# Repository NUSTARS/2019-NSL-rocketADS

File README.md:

# rocketADS
Software and Hardware for an active drag system for the Nasa Student Launch Competition

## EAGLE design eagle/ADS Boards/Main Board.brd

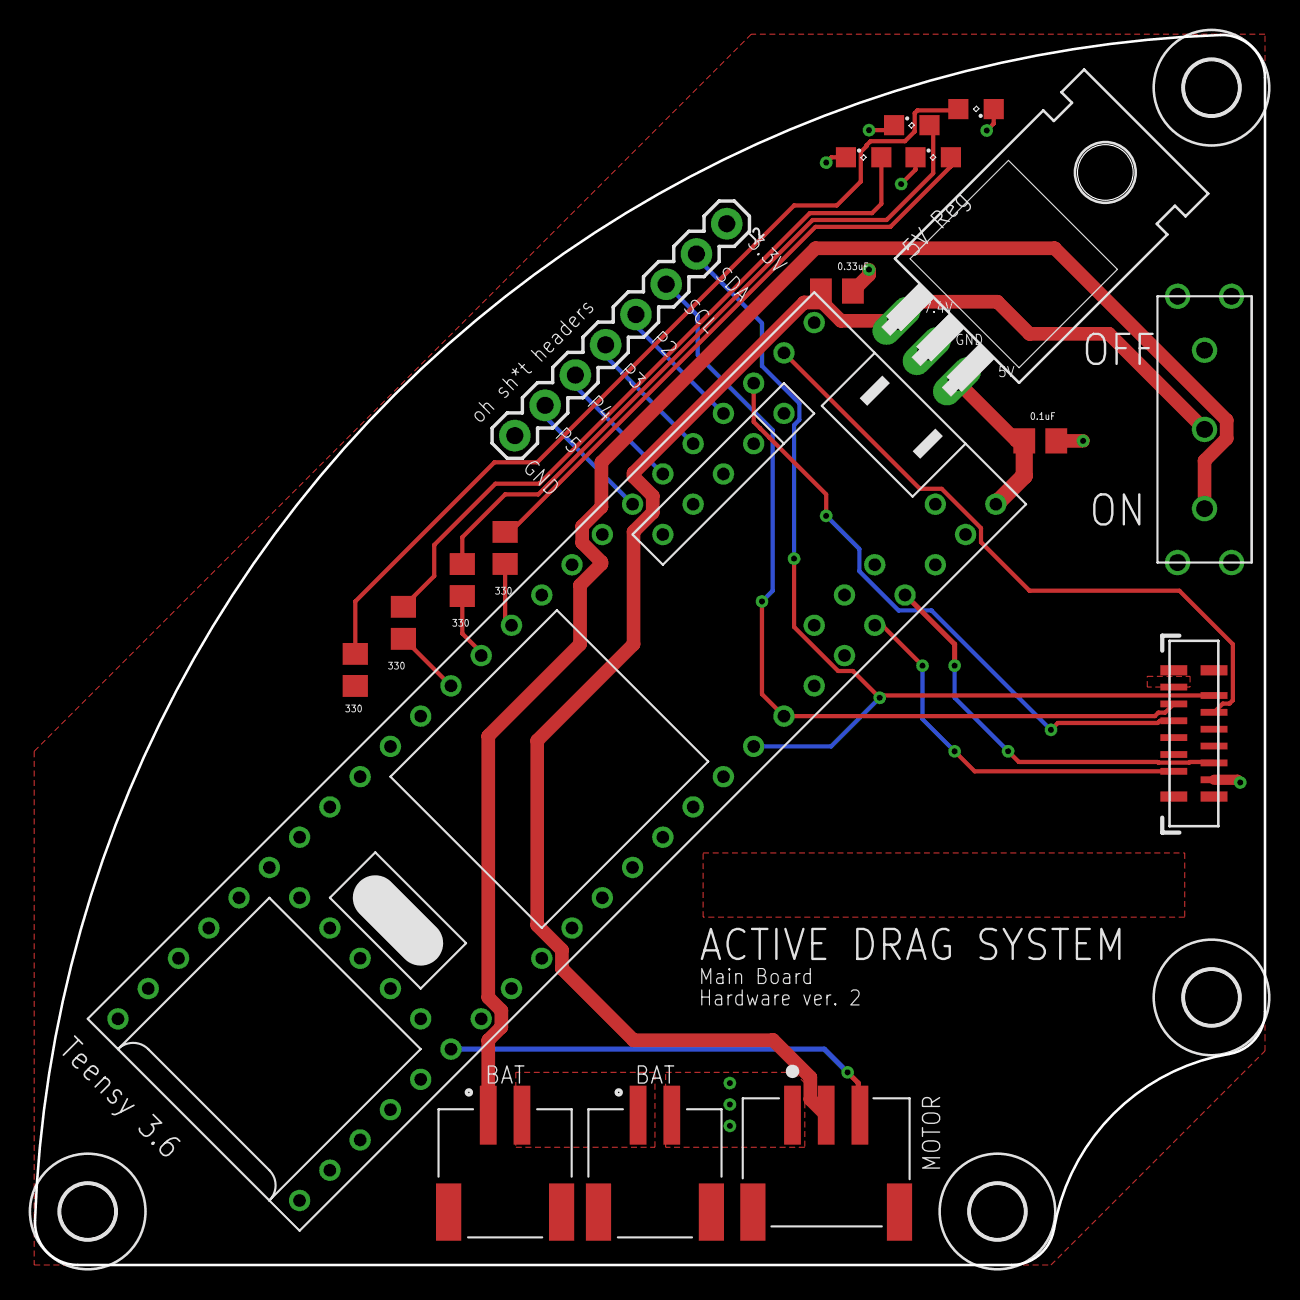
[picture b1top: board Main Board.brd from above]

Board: 2 copper layers, 73.0 x 73.0 mm, 22 parts (0 on the bottom side), 24 nets.

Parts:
BATTERY1, BATTERY2: S2B-PH-SM4-TB(LF)(SN); JST_S2B-PH-SM4-TB(LF)(SN)
C3: 0.33uF; C0805
C4: 0.1uF; C0805
H1, H2, H3, H4: MOUNT-HOLE3.2; 3,2
IC1: 7808T; TO220H
J1: 62674-121121ALF; CON12_1X12_DUT_58XF
J2: 1X08
LED1, LED2, LED3, LED4: SML0805
MOTOR: S3B-PH-SM4-TB(LF)(SN); JST_S3B-PH-SM4-TB(LF)(SN)
R1, R2, R3, R4: 330; R0805
U$1: TEENSY3.6
U$4: SLIDE_SWITCH2

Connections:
3.3V: J1.1, J2.1, R1.2, U$1.3.3V0, U$1.3.3V1, U$1.3.3V2
5V: C4.1, IC1.3, U$1.VIN
ADR: J1.11, U$1.P22
B1: J1.4, U$1.P0
B2: J1.5, U$1.P1
B3: J2.4, U$1.P2
B4: J2.5, U$1.P3
B5: J2.6, U$1.P4
B6: J2.7, U$1.P5
ERROR_LED: R3.2, U$1.P10
GND: BATTERY1.2, C3.2, C4.2, IC1.2, J1.12, J2.8, LED1.C, LED2.C, LED3.C, LED4.C, MOTOR.1, U$1.GND, U$1.GND0, U$1.GND2, U$4.OUT1
MISC_LED: R4.2, U$1.P11
MOTOR: MOTOR.3, U$1.P38
unnamed: LED1.A, R1.1
unnamed: BATTERY1.1, BATTERY2.2
unnamed: LED2.A, R2.1
unnamed: LED3.A, R3.1
unnamed: LED4.A, R4.1
RST: J1.10, U$1.P23
SCL: J1.3, J2.3, U$1.P19
SDA: J1.2, J2.2, U$1.P18
STATUS_LED: R2.2, U$1.P9
V_BATT: BATTERY2.1, U$4.OUT2
V_IN: C3.1, IC1.1, MOTOR.2, U$4.IN

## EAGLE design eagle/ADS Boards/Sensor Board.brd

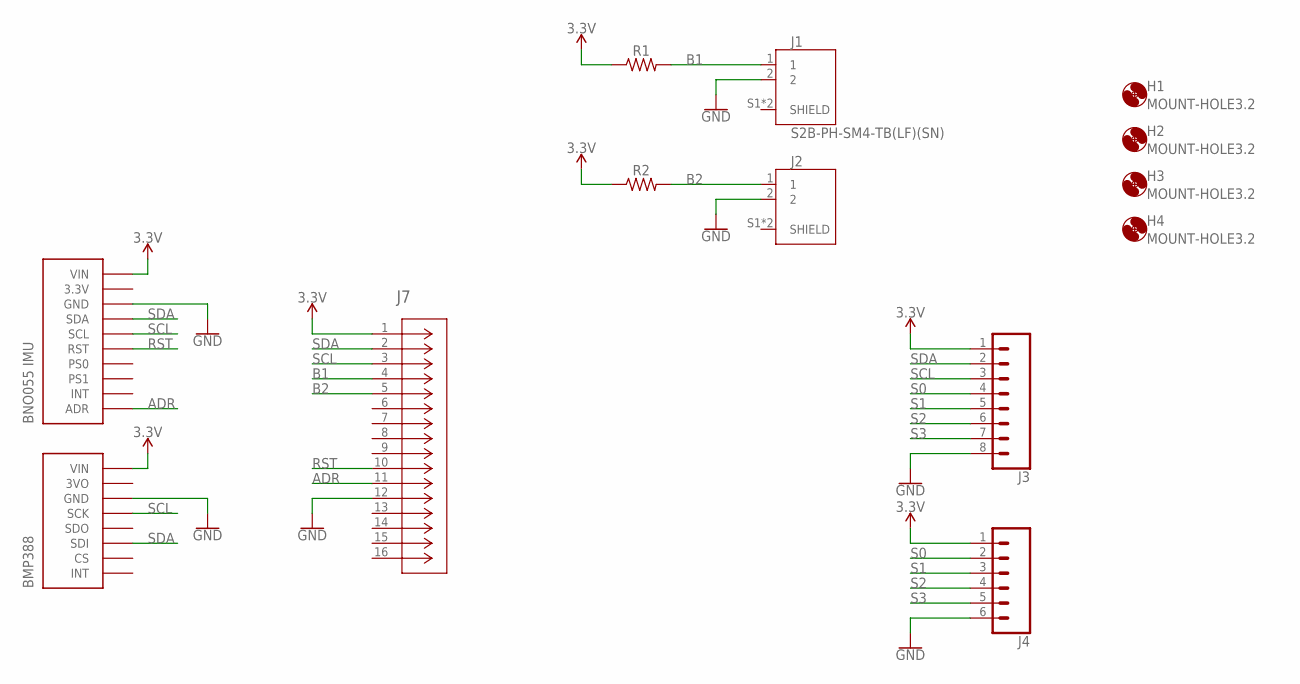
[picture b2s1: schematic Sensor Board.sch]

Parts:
H1, H2, H3, H4: MOUNT-HOLE3.2; 3,2
J1, J2: S2B-PH-SM4-TB(LF)(SN); JST_S2B-PH-SM4-TB(LF)(SN)
J3: CONN_08"; 1X08
J4: CONN_06SILK_FEMALE_PTH; 1X06
J7: 62674-121121ALF; CON12_1X12_DUT_58XF
R1, R2: 10k; R0805
U$1: BMP388
U$2: BNO055

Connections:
3.3V: J3.1, J4.1, J7.1 (11), R1.1, R2.1, U$1.VIN, U$2.VIN
ADR: J7.11 (1111), U$2.ADR
B1: J1.1, J7.4 (44), R1.2
B2: J2.1, J7.5 (55), R2.2
GND: J1.2, J2.2, J3.8, J4.6, J7.12 (1212), U$1.GND, U$2.GND
RST: J7.10 (1010), U$2.RST
S0: J3.4, J4.2
S1: J3.5, J4.3
S2: J3.6, J4.4
S3: J3.7, J4.5
SCL: J3.3, J7.3 (33), U$1.SCK, U$2.SCL
SDA: J3.2, J7.2 (22), U$1.SDI, U$2.SDA

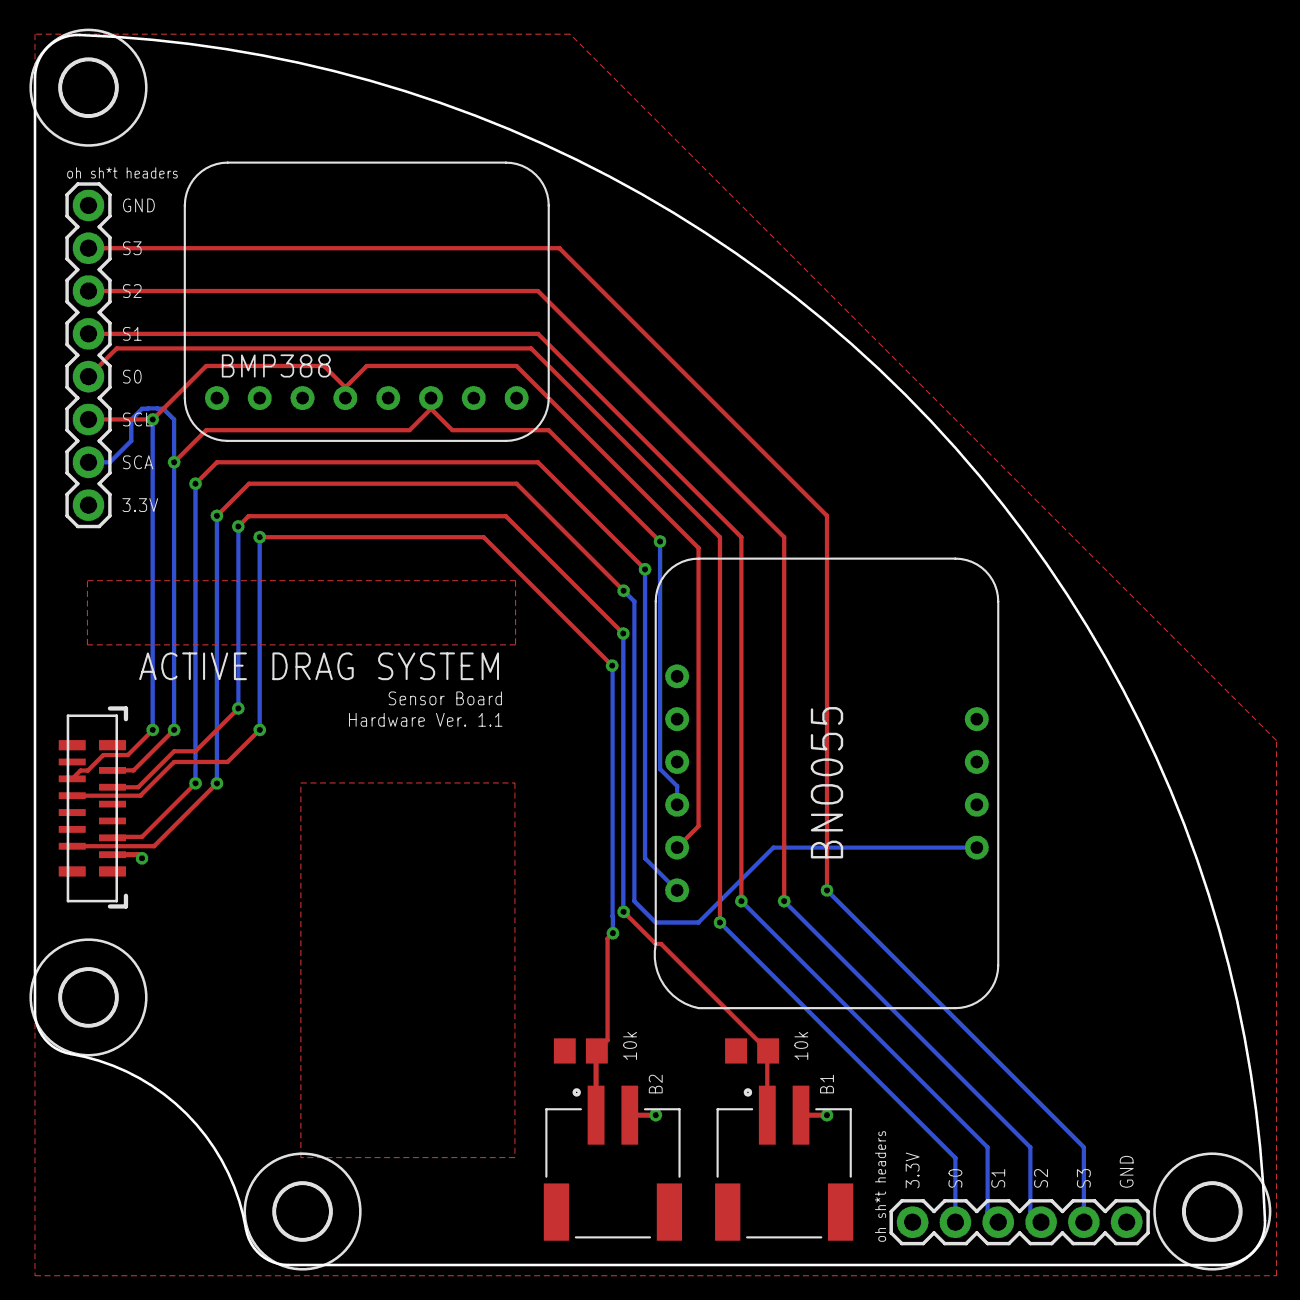
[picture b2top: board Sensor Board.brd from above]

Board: 2 copper layers, 73.0 x 73.0 mm, 13 parts (0 on the bottom side), 12 nets.

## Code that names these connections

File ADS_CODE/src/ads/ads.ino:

//#include <pid.h>
#include "sensors.h"
#include "storage.h"
#include <string>
#include <Servo.h>


#define STATUS_LED 10
#define ERROR_LED 9
#define BUILT_IN_LED 13
#define MISC_LED 11

#define BURNOUT_TIME 3500
#define APOGEE_TIME  17000

#define SERVO_CLOSE 750 //TODO: see if this can be used elsewhere in the code, as there are references to 750 where this is not used
#define SERVO_OPEN 2248

#define CLOSED_SERVO_PIN 0
#define OPEN_SERVO_PIN 1

#define SERVO_STEP_SIZE 50

using namespace nustars;


IntervalTimer timer;
IntervalTimer saveTimer;
IntervalTimer servoTimer;

bool errorFlag = false;
uint8_t testBit = 0;
byte value = 0;
int timerCounter = 0;

bool inFlight = false;
uint32_t flightTimestamp = 0;
bool postBurnout = false;
bool postApogee = false;

//SERVO VARS
Servo myservo; //NOTE: shouldn't need to be volatile as this is not a mutable class
volatile int servoRequestPosition;    //volatility required as per wiki for interrupt pin functions
int actualServoPosition;
byte servoLimits = 0;

void setup() {

    timer.begin(processLoop, 20000);
    servoTimer.begin(servoLoop, 5000); //TODO: change this to an appropriate value; we want it to be slow enough to allow the servo time to update but fast enough that it will move quickly
    saveTimer.begin(saveLoop, 15000000);
    myservo.attach(38);
    servoRequestPosition = (SERVO_OPEN + SERVO_CLOSE) >> 1;
    actualServoPosition = servoRequestPosition;
    myservo.writeMicroseconds(actualServoPosition); //set the servo to its middle position, which should be definitely safe

    //todo: read calibration data in from previous runs for accelerometers

    //assuming the pins are pulled normally high and also I forgot the specifics of the switches so this is general for now...
    pinMode(OPEN_SERVO_PIN, INPUT);
    pinMode(CLOSED_SERVO_PIN, INPUT);
    attachInterrupt(digitalPinToInterrupt(CLOSED_SERVO_PIN), interruptServoClosed, CHANGE);
    attachInterrupt(digitalPinToInterrupt(OPEN_SERVO_PIN), interruptServoOpen, CHANGE);
}

//todo: check for verticalness of rocket and only start timer at that point.
//todo: dont start save loop until flight start
void loop() {
    //intentionally blank
}

void saveLoop() {
    Serial.println(digitalRead(CLOSED_SERVO_PIN));
}

void processLoop() {

    if (servoRequestPosition > SERVO_OPEN) servoRequestPosition = SERVO_CLOSE;
    servoRequestPosition += 100;
    Serial.println(servoLimits);

}

/**
 * Update the servo position intelligently.
 * Keep track of actual servo position while handling requested position, allowing us to easily correct for over/underextension
 */
void servoLoop() {
    servoRequestPosition -= servoRequestPosition % SERVO_STEP_SIZE;
    if (servoRequestPosition == actualServoPosition) return;
    int dir = servoRequestPosition < actualServoPosition ? -1 : 1;
    dir *= SERVO_STEP_SIZE;
    dir -= SERVO_STEP_SIZE * (dir > 0 && (servoLimits & 1));
    dir += SERVO_STEP_SIZE * (dir < 0 && (servoLimits & 2));
    actualServoPosition += dir;
    if (actualServoPosition > SERVO_OPEN) actualServoPosition = SERVO_OPEN;
    else if (actualServoPosition < SERVO_CLOSE) actualServoPosition = SERVO_CLOSE;
    myservo.writeMicroseconds(actualServoPosition);
}

/**
 * When the overextension limit switch changes, update its limit bit
 */
void interruptServoOpen() {
    servoLimits &= ~1;
    servoLimits |= !digitalRead(OPEN_SERVO_PIN);
}

/**
 * When the underextension limit switch changes, update its limit bit
 */
void interruptServoClosed() {
    servoLimits &= ~2;
    servoLimits |= !digitalRead(CLOSED_SERVO_PIN) << 1;
}

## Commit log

2018-12-26 Eagle Schematics for Sensor and Main Boards
2018-12-26 Add .gitignore file
2018-12-26 Clean up backup files
2018-12-26 clean up a git mess
2018-12-27 Finish Preliminary Board Layouts
2018-12-27 Convert .dxf files to imperial units
2019-01-13 Modify to surface mount components
2019-01-24 Convert to SMD components still needs to be done
2019-01-27 Finalized Boards, Gerbers, and DXF files.
2019-02-08 Added a tester code or whatever
2019-02-08 Fixed storage constructor
2019-02-08 Raw Data Read Test
2019-02-08 Sample Code Datalogging
2019-02-08 WOrking Datalogger
2019-02-08 Datalogger Status LEDS implemented, saving fixed, formatting fixed, optimized execution
2019-02-10 Launch Configuration
2019-02-10 Upload 2-9 Launch Data
2019-02-10 modified code
2019-02-10 battery percentage checks
2019-02-10 adding
2019-02-10 minor test changes
2019-02-10 more test
2019-02-10 test
2019-02-10 finish
2019-02-12 "Starting the ads Simulink file."
2019-02-16 fixed rocket boards
2019-02-16 rename several folders for arduino compatibility
2019-02-16 make workspace
2019-02-16 Create overall structure for code
2019-02-22 reverting datalogger back to working launch configuration
2019-02-22 Working ADS motor actuation
2019-03-02 ADS Launch Config
2019-03-03 Fixed some formatting, corrected small memory leak, added prototype interrupt code
2019-03-20 Interrupts and servo control regulation

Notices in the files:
parts and their libraries:
SparkFun-Connectors: Licensing: Creative Commons ShareAlike 4.0 International - https://creativecommons.org/licenses/by-sa/4.0
